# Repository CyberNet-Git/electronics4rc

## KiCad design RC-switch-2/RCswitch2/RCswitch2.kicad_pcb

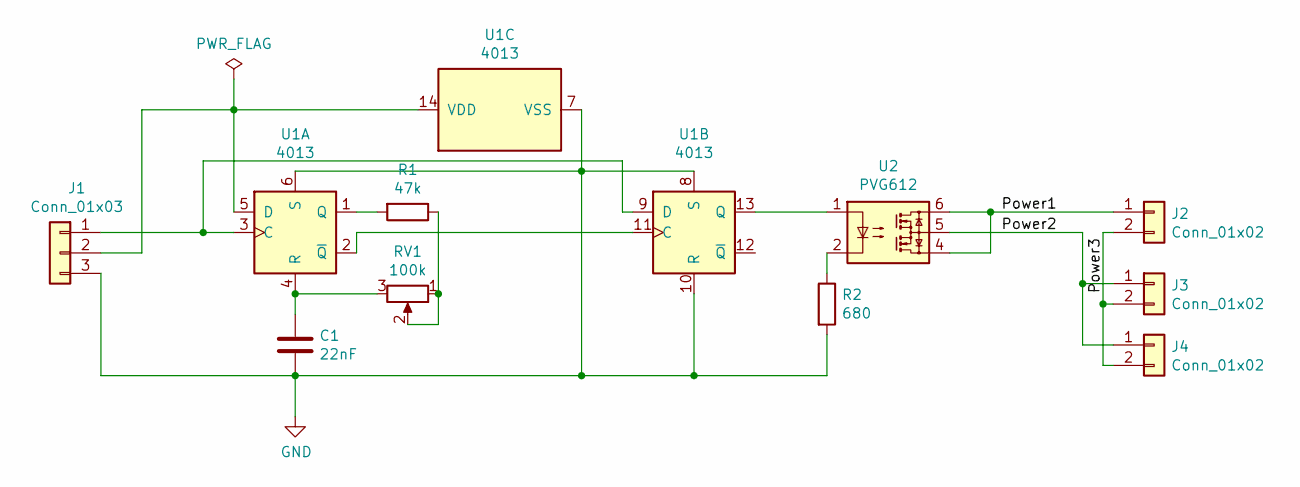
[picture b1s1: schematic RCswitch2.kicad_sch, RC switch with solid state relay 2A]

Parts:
C1: 22nF; C_0805_2012Metric_Pad1.15x1.40mm_HandSolder
J1: Conn_01x03; PinHeader_1x03_P2.54mm_Vertical
J2, J3, J4: Conn_01x02; Molex_KK-254_AE-6410-02A_1x02_P2.54mm_Vertical
R1: 47k; R_0603_1608Metric_Pad1.05x0.95mm_HandSolder
R2: 680; R_0805_2012Metric_Pad1.15x1.40mm_HandSolder
RV1: 100k; Potentiometer_Bourns_3314G_Vertical
U1: 4013; SOIC-14_3.9x8.7mm_P1.27mm
U2: PVG612; SMDIP-6_W9.53mm

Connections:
/Power1: J2.1, U2.4, U2.6
/Power2: J3.1, J4.1, U2.5
/Power3: J2.2, J3.2, J4.2
GND: C1.2, J1.3, R2.2, U1.6 (S), U1.7 (VSS), U1.8 (S), U1.10 (R)
unnamed: C1.1, RV1.3, U1.4 (R)
unnamed: J1.1, U1.3 (C), U1.9 (D)
unnamed: J1.2, U1.5 (D), U1.14 (VDD)
unnamed: R1.1, RV1.1, RV1.2
unnamed: R1.2, U1.1 (Q)
unnamed: R2.1, U2.2
unnamed: U1.2 (~Q), U1.11 (C)
unnamed: U1.13 (Q), U2.1

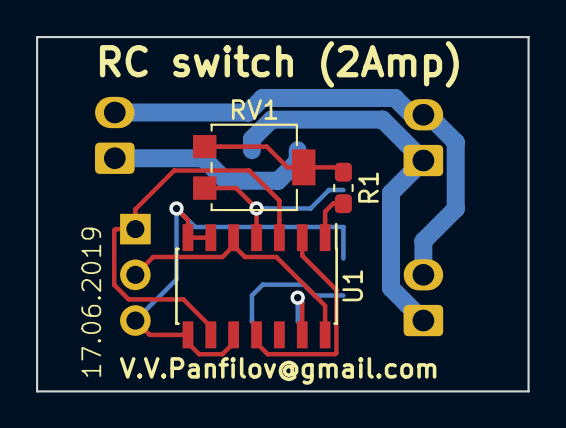
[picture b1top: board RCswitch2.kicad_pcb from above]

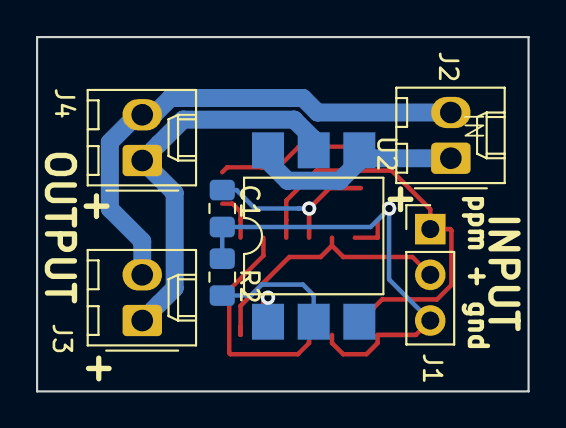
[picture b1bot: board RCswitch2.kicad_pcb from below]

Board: 2 copper layers, 27.3 x 19.7 mm, 10 parts (7 on the bottom side), 12 nets.

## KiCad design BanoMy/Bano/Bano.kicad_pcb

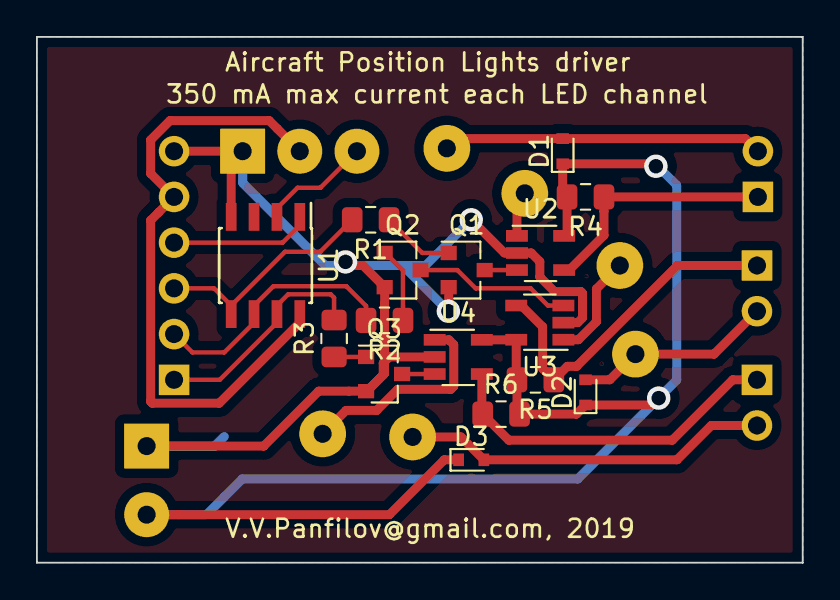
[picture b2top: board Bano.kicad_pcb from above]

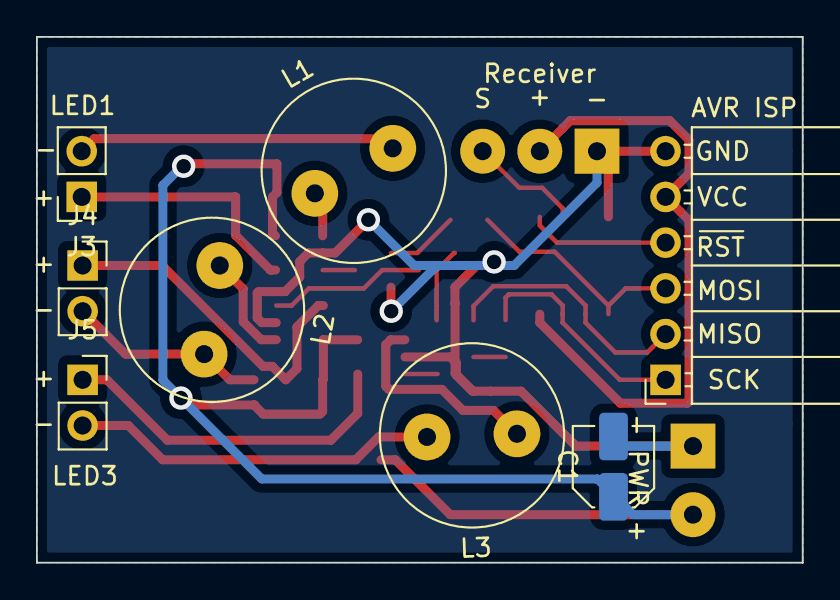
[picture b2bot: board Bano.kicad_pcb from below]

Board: 2 copper layers, 42.5 x 29.2 mm, 26 parts (10 on the bottom side), 23 nets.

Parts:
- PWR +: 3S LiPO; SolderWirePad_1x02_P3.81mm_Drill1mm
AVR ISP: PROGRAM; PinSocket_1x06_P2.54mm_Horizontal
C1: 4.7uF; C_Elec_4x5.4
D1, D2, D3: SS12; D_SOD-523
J3: LED1; PinSocket_1x02_P2.54mm_Vertical
J4: LED2; PinSocket_1x02_P2.54mm_Vertical
J5: LED3; PinSocket_1x02_P2.54mm_Vertical
L1, L2, L3: 47uh; L_Radial_D10.0mm_P5.00mm_Fastron_07M
Q1, Q2, Q3: BC817; SOT-23
R1, R2, R3: 10K; R_0805_2012Metric_Pad1.15x1.40mm_HandSolder
R4, R5, R6: 0,33; R_0805_2012Metric_Pad1.15x1.40mm_HandSolder
Receiver: PPM; SolderWirePad_1x03_P3.175mm_Drill1mm
U1: ATtiny13A-SSU; SOIC-8_3.9x4.9mm_P1.27mm
U2, U3, U4: ZXLD1350; TSOT-23-5

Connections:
+12V: - PWR +.2, C1.1, D1.1, D2.1, D3.1, R4.2, R5.2, R6.2, U2.5, U3.5, U4.5
+BATT: AVR ISP.5, Receiver.2, U1.8
/LED1+: J3.1, R4.1, U2.4
/LED1-: D1.2, J3.2, L1.2
/LED1-ADJ: Q1.3, U2.3
/LED2+: J4.1, R5.1, U3.4
/LED2-: D2.2, J4.2, L2.2
/LED2-ADJ: Q2.3, U3.3
/LED3+: J5.1, R6.1, U4.4
/LED3-: D3.2, J5.2, L3.2
/LED3-ADJ: Q3.3, U4.3
/PB0(MOSI): AVR ISP.3, R1.2, U1.5
/PB1(MISO): AVR ISP.2, R2.2, U1.6
/PB2(SCK): AVR ISP.1, R3.2, U1.7
/PPM-Signal: Receiver.3, U1.2
/RST: AVR ISP.4, U1.1
GND: - PWR +.1, AVR ISP.6, C1.2, Q1.2, Q2.2, Q3.2, Receiver.1, U1.4, U2.2, U3.2, U4.2
unnamed: L1.1, U2.1
unnamed: L2.1, U3.1
unnamed: L3.1, U4.1
unnamed: Q1.1, R1.1
unnamed: Q2.1, R2.1
unnamed: Q3.1, R3.1

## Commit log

2009-10-06 Initial directory structure.
2009-10-06 Initial load of source files
2009-10-07 Changed IC type
2009-10-07 Working on new modules
2009-10-11 PCB ready. Need more check.
2009-10-11 Added TODO.txt in UTF-8 written in Russian.
2009-10-12 Changed PCB a little. Moved and resized some pads. Multiplied schemes over the whole page.
2009-10-12 Added rendered ps files for copper and componet layers
2009-10-12 Previous files converted to pdf
2009-10-12 Vias modified - enlarget up to 2mm, other pad too. Tracks relocated. It is very difficult to make accurate drills by hands.
2009-10-15 Redesigning PCB due to one big error. PDIP package was used for designing TQFP PCB. ARGHHH. All over again.
2015-03-14 Migrating wiki contents from Google Code
2019-05-12 Initially added Bano project
2019-05-12 Initially added Bano-IL-86 and RCSwitch projects
2019-06-16 working PPM+PWM, working on full control circle with mix on Tx for B-channel led intencity
2019-06-17 Added RCswitch-2 Kicad project
2019-06-18 Done with RCswitch2. Production is ordered from JLCPCB
2025-06-01 Added old RCSwitch-2 project for my friend S.Koslovsky
